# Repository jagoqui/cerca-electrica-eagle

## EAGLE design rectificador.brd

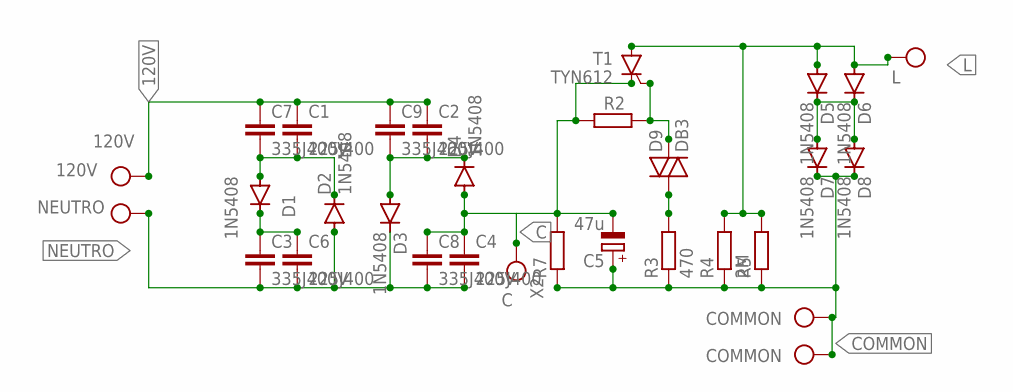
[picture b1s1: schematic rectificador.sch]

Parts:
C1, C2, C4, C6: 225J400; C15B9
C3, C7, C8, C9: 335J400V; C15B9
C5: 47u; E2-5; MPN V3-WM-E2-5M-PUR
D1, D2, D3, D4, D5, D6, D7, D8: 1N5408; DO201-15
D9: DB3; DO35-10
R2, R5, R7: R-EU_0207/10; 0207/10
R3: 470; 0207/10
R4: 2M; 0207/10
T1: TYN612; TO220CS
VIN: 120V; W237-102
X2: X2; W237-4

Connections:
120V: C1.1, C2.1, C7.1, C9.1, VIN.2
C: C4.1, C5.-, C8.1, D4.A, R2.1, R7.2, T1.C, X2.4
COMMON: C5.+, D7.C, D8.C, R3.1, R4.1, R5.1, R7.1, X2.2, X2.3
L: D5.A, D6.A, R4.2, R5.2, T1.A, X2.1
unnamed: D9.A (1), R3.2
unnamed: C3.1, C6.1, D1.C
unnamed: C2.2, C9.2, D3.A, D4.C
unnamed: C1.2, C7.2, D1.A, D2.C
unnamed: D5.C, D6.C, D7.A, D8.A
unnamed: D9.C (2), R2.2, T1.G
NEUTRO: C3.2, C4.2, C6.2, C8.2, D2.A, D3.C, VIN.1

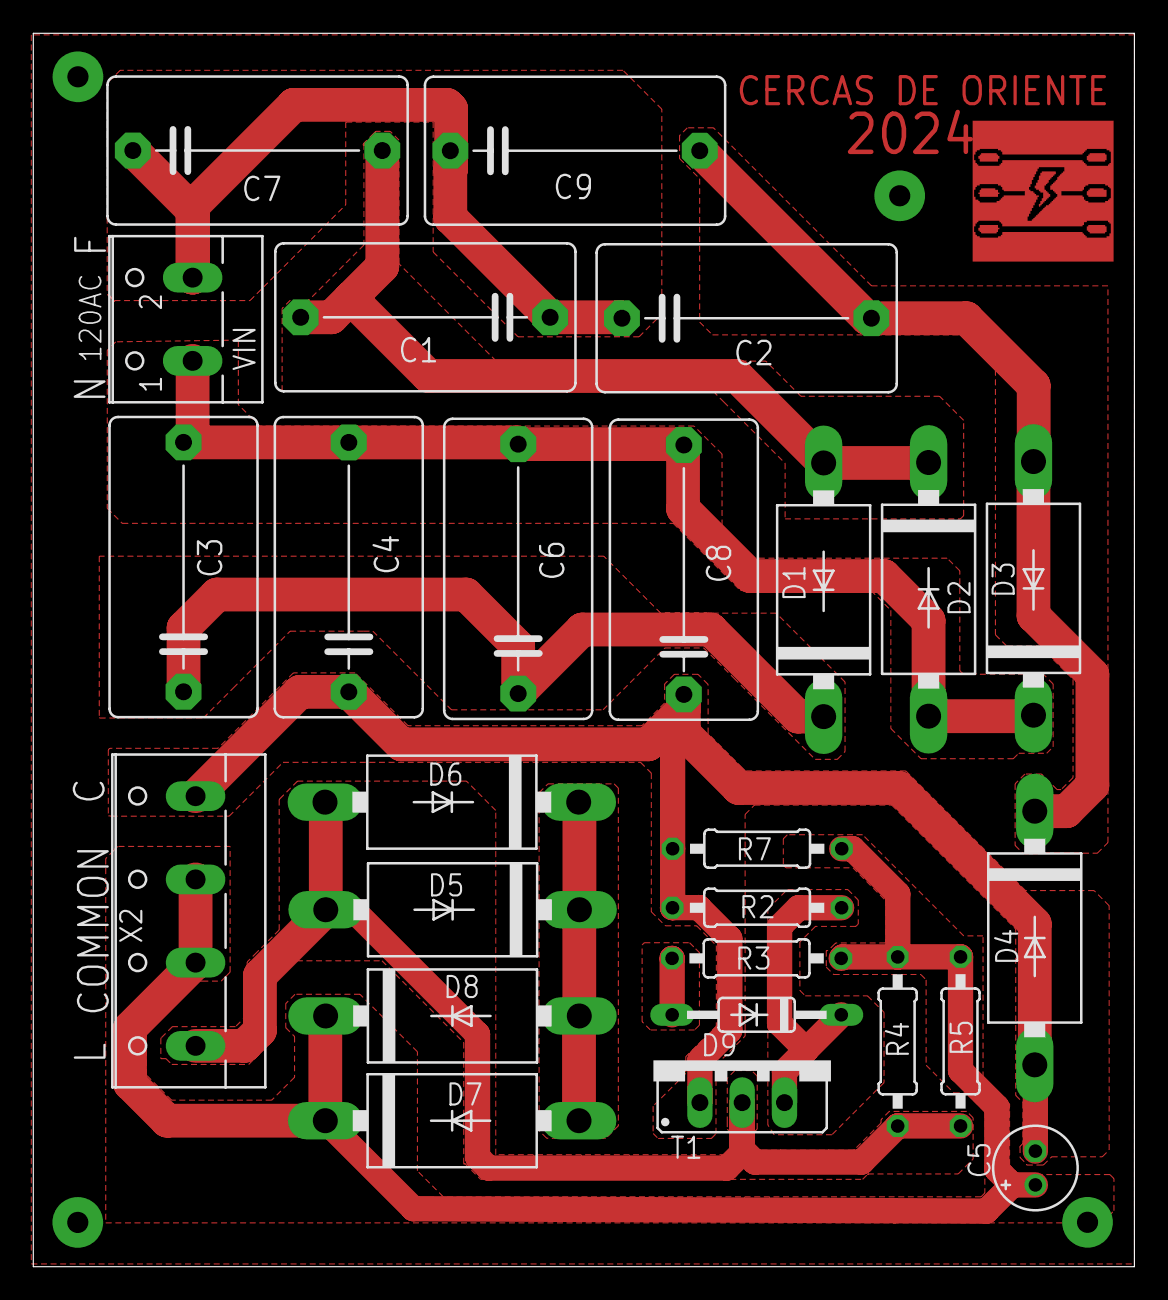
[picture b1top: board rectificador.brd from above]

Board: 2 copper layers, 66.2 x 74.1 mm, 26 parts (0 on the bottom side), 11 nets.

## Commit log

2024-09-10 feat: create shemactics and design of electric wall.
2024-09-11 feat: add 3D packages.
